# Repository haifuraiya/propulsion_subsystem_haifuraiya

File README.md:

# propulsion_subsystem_haifuraiya
# Introduction

This Open Research Institute Phase4SPace project repo will be used to develop the proposed Haifuraiya (Japanese:  ハイフライヤー English: High-Flyer) propulsion subsystem for a future HEO mission SmallSat. The repo was created on 8/28/2022.

# Summary

In July/August 2022 the ORI community discussed formalizing a concept for a High Energy Orbit (HEO) 'flyer' satellite, that would have its own propulsion system. The background for the Haifuraiya name and the overall initial concept derivation/top-level goals was discussed at length and is recorded[^1] and its predecessor concept by Jan King W3GEY is directly available[^2]. 

# Team

1. Samudra Haque N3RDX
2. Dan Schultz N8FGV
3. Thomas Denz, KC3ELI

# Special Notes

By special arrangement with its inventor/develpoer, ORI is making available in this repository a public copy of the entire flight hardware designs/firmware build knowledge-base including a comprehensive technical, scientific and industrial documentation set of [The George Washington University][100] [Micro-propulsion and Nanotechnology Laboratory][99]'s successful 2014-2015 BRICSAT-P (US Naval Academy/George Washington University) and 2014-2018 Canyval-X (Yonsei University/NASA GSFC/George Washington University) CubeSat quad-channel electric rocket system as provided in 2015 to NASA, on the condition that it is only used for study/research/experimentation/academic and scientific missions, and no commercial development is allowed. Parts of the technology have been patented (US Patent 10006445) and is available for licensing from The George Washington University. 

The knowledge-base is available [here][101]

If you choose to view/utilize the references (Approximately *3.14GB, 3525 files*), you are advised the knowledge-base contains copyrighted code, and information that was and still could be of a propietary nature thus may have more restrictive licenses than the license under which ORI has organized this repository. Your are restricted from disseminating this repository without the exact same restrictions you are being asked to follow. *While ORI has assurances the information will be able to be replicated (to build ground/engineering/flight hardware) with current production COTS parts -  there is no technical support provided, and all questions are to be redirected to the inventor/developer directly. Contact ORI for further details.* 

# References

[^1]: [Haifuraiya slide presentations (August 2022)][1]
[^2]: [HEO-F Mission Overview Space System Design Concept (November 3, 2014)]

[1:] https://github.com/phase4ground/documents/tree/master/Papers_Articles_Presentations/Slide_Presentations/haifuraiya/   
[2:] https://github.com/phase4ground/documents/blob/master/Papers_Articles_Presentations/Slide_Presentations/haifuraiya/HEO-F_Mission%20Overview.pptx  
[99:] https://mpnl.seas.gwu.edu/  
[100:] https://www.gwu.edu  
[101:] TBD

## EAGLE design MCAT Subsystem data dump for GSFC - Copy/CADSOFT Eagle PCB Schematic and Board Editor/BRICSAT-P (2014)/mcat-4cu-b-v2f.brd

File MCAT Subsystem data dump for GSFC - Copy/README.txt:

This folder is intended to assist NASA GSFC team in debugging/repairing/replacing MCAT Subsystem hardware for the CANYVAL-X mission.

Portions of the content are (c) The George Washington University, 2015. Patents-pending. Some of the information of this folder is covered under US Patent 20110258981 and US Patent Appl 14/462,127, and possibly others. 

Embedded Firmware included in this release is (c) The George Washington University, 2013-2015.

Release of this information to NASA has been cleared by GWU Office of Technology Transfer, to aid in troubleshooting the CANYVAL-X mission hardware.

For information about updated copyright/patent status please contact: 

Gus Williamson
Licensing Associate-Physical Sciences  | Office of Technology Transfer                      
The George Washington University  | 2033 K St, NW;  Suite 750; Washington, DC 20052
T: +1-202-994-8975  M: +1-443-824-9692  | Email: gwilliamson@gwu.edu

For technical information:

Michael Keidar
Professor of Mechanical and Aerospace Engineering
School of Engineering and Applied Science
Professor of Neurological Surgery, School of Medicine and Health Sciences
Director, GW Institute for Nanotechnology
The George Washington University
Science & Engineering Hall 3550
800 22nd Street, Northwest
Washington, DC 20052
tel: 202-994-6929; fax: 202-994-0238
email: keidar@gwu.edu
https://www.mpnl.seas.gwu.edu

Additional testing/analytical data can be obtained from:

Samudra Haque, Ph.D Candidate, Aerospace Engineering, samudra@gwu.edu, (202) 812-3325

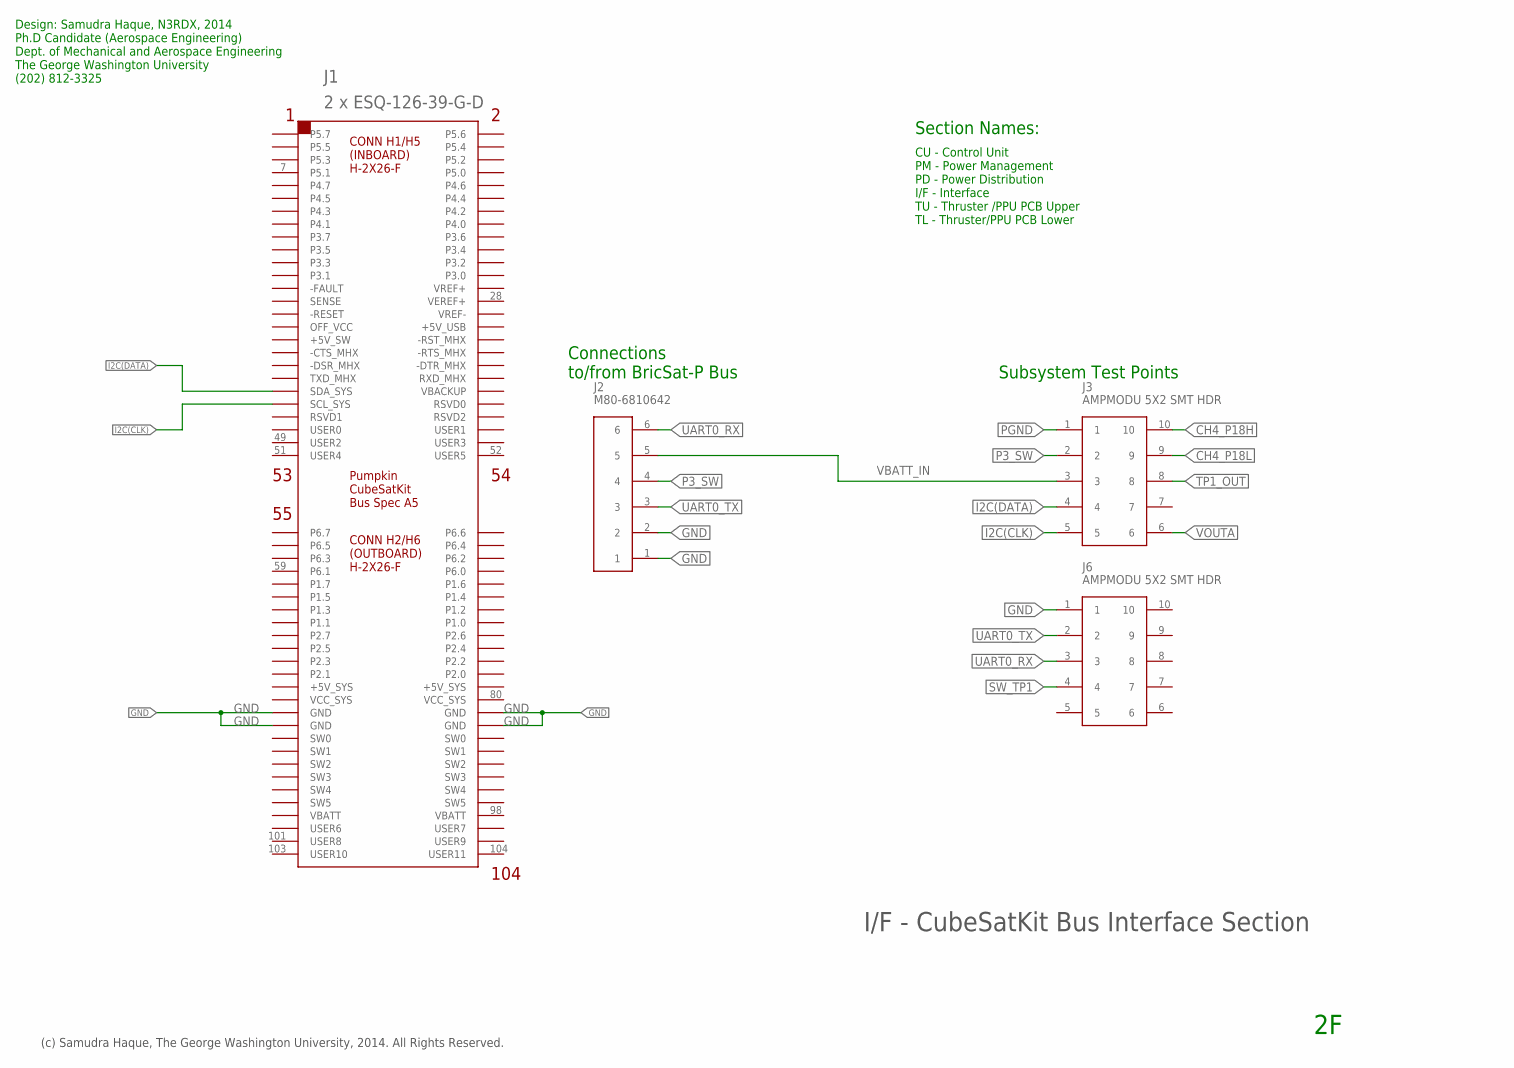
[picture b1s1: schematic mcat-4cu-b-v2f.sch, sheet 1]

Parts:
J1: 2 x ESQ-126-39-G-D; CSK-BUS-PKG
J2: M80-6810642; M80-68106
J3, J6: AMPMODU 5X2 SMT HDR; AMPMODU-SMT-PIN-HEADER-5X2

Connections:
CH4_P18H: J3.10; also elsewhere on the board
CH4_P18L: J3.9; also elsewhere on the board
GND: J1.81 (GND), J1.82 (GND), J1.83 (GND), J1.84 (GND), J2.1, J2.2, J6.1; also elsewhere on the board
I2C(CLK): J1.43 (SCL_SYS), J3.5; also elsewhere on the board
I2C(DATA): J1.41 (SDA_SYS), J3.4; also elsewhere on the board
P3_SW: J2.4, J3.2; also elsewhere on the board
PGND: J3.1; also elsewhere on the board
SW_TP1: J6.4; also elsewhere on the board
TP1_OUT: J3.8; also elsewhere on the board
UART0_RX: J2.6, J6.3; also elsewhere on the board
UART0_TX: J2.3, J6.2; also elsewhere on the board
VBATT_IN: J2.5, J3.3; also elsewhere on the board
VOUTA: J3.6; also elsewhere on the board

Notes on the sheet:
I/F - CubeSatKit Bus Interface Section
Subsystem Test Points
(c) Samudra Haque, The George Washington University, 2014. All Rights Reserved.
Connections to/from BricSat-P Bus
Design: Samudra Haque, N3RDX, 2014 Ph.D Candidate (Aerospace Engineering) Dept. of Mechanical and Aerospace Engineering The George Washington University (202) 812-3325
Section Names:
CU - Control Unit PM - Power Management PD - Power Distribution I/F - Interface TU - Thruster /PPU PCB Upper TL - Thruster/PPU PCB Lower

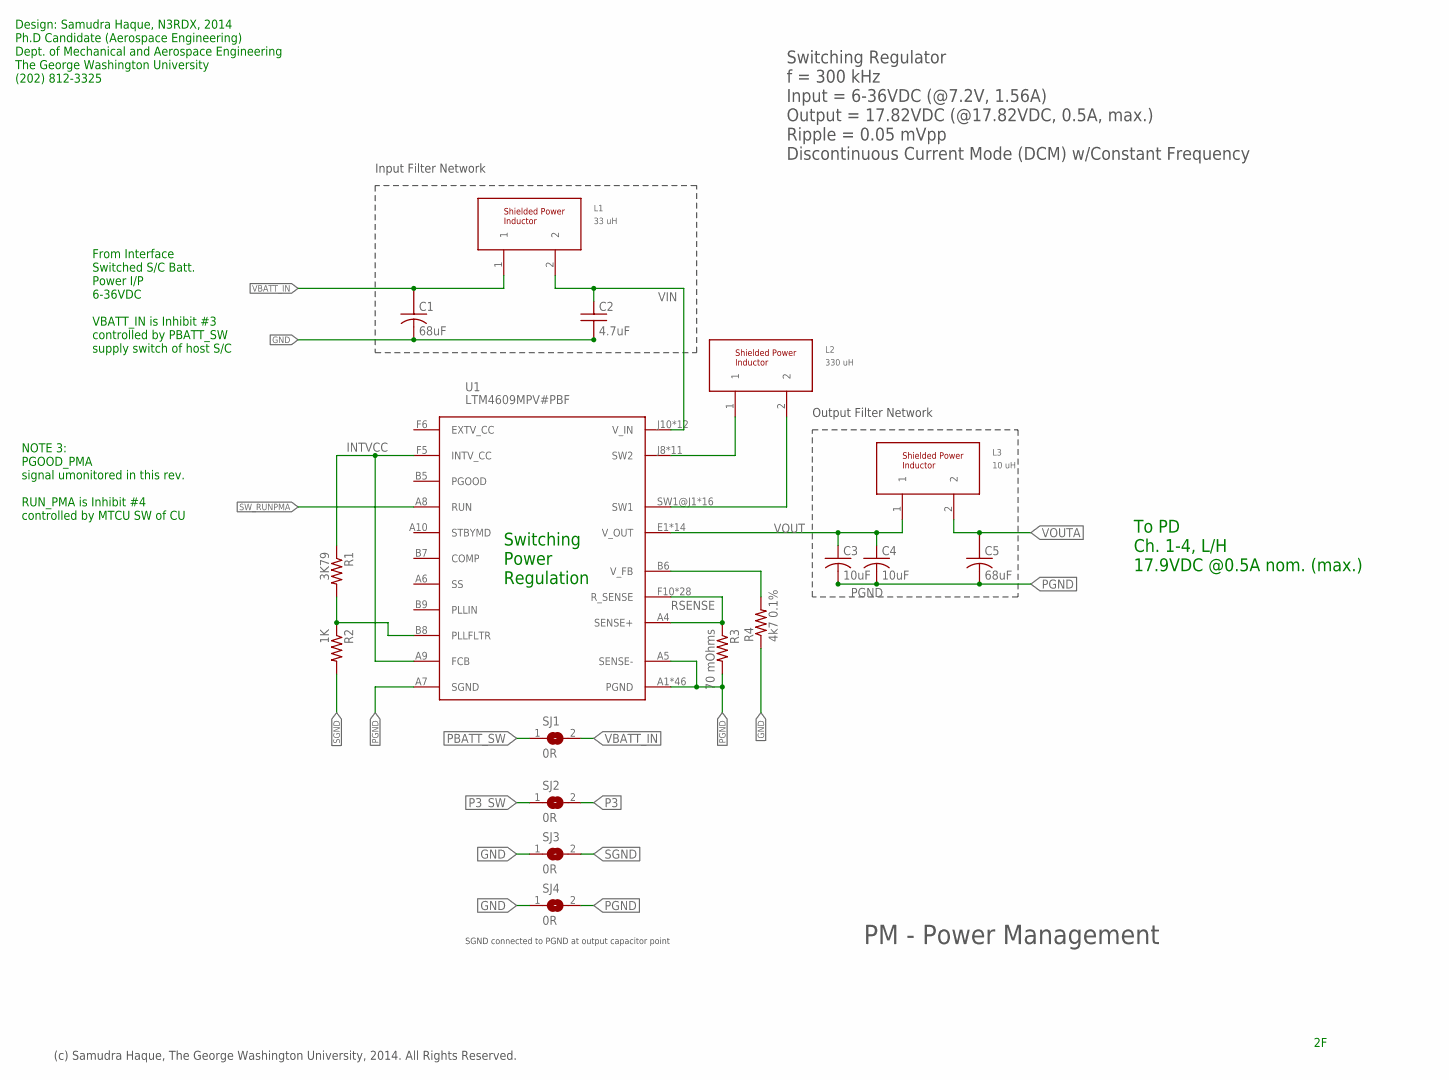
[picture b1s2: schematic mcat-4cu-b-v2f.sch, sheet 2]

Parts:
C1, C5: 68uF; OS-CON-SVPF-F12
C2: 4.7uF; MLCC-X7R-1210
C3, C4: 10uF; C1210K
L1: 33 uH; MSS1048
L2: 330 uH; MSS1048
L3: 10 uH; SERIES-POWER-INDUCTORS
R1: 3K79; R0805
R2: 1K; R0805
R3: 70 mOhms; R1206
R4: 4k7 0.1%; R0603
SJ1, SJ2, SJ3, SJ4: 0R; SJ
U1: LTM4609MPV#PBF; LGA-141-LTC-05-08-1840-B

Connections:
GND: C1.K1 (K), C2.2, R4.1, SJ3.1, SJ4.1; also elsewhere on the board
INTVCC: R1.1, U1.A9 (FCB), U1.F5 (INTV_CC)
P3: SJ2.2; also elsewhere on the board
P3_SW: SJ2.1; also elsewhere on the board
PBATT_SW: SJ1.1
PGND: C3.2, C4.2, C5.K1 (K), R3.2, SJ4.2, U1.A1 (PGND), U1.A2 (PGND), U1.A3 (PGND), U1.A5 (SENSE-), U1.A7 (SGND), U1.A11 (PGND), U1.A12 (PGND), U1.B1 (PGND), U1.B2 (PGND), U1.B3 (PGND), U1.B4 (PGND), U1.B10 (PGND), U1.B11 (PGND), U1.B12 (PGND), U1.C1 (PGND), U1.C2 (PGND), U1.C3 (PGND), U1.C4 (PGND), U1.C5 (PGND), U1.C6 (PGND), U1.C7 (PGND), U1.C8 (PGND), U1.C9 (PGND), U1.C10 (PGND), U1.C11 (PGND), U1.C12 (PGND), U1.D1 (PGND), U1.D2 (PGND), U1.D3 (PGND), U1.D4 (PGND), U1.D5 (PGND), U1.D6 (PGND), U1.D7 (PGND), U1.D8 (PGND), U1.D9 (PGND), U1.D10 (PGND), U1.D11 (PGND), U1.D12 (PGND), U1.E3 (PGND), U1.E4 (PGND), U1.E5 (PGND), U1.E6 (PGND), U1.E7 (PGND), U1.E8 (PGND), U1.E9 (PGND), U1.E10 (PGND), U1.E11 (PGND), U1.E12 (PGND); also elsewhere on the board
RSENSE: R3.1, U1.A4 (SENSE+), U1.F10 (R_SENSE), U1.F11 (R_SENSE), U1.F12 (R_SENSE), U1.G5 (R_SENSE), U1.G6 (R_SENSE), U1.G7 (R_SENSE), U1.G8 (R_SENSE), U1.G9 (R_SENSE), U1.G10 (R_SENSE), U1.G11 (R_SENSE), U1.G12 (R_SENSE), U1.H5 (R_SENSE), U1.H6 (R_SENSE), U1.H7 (R_SENSE), U1.H8 (R_SENSE), U1.H9 (R_SENSE), U1.H10 (R_SENSE), U1.H11 (R_SENSE), U1.H12 (R_SENSE), U1.J5 (R_SENSE), U1.J6 (R_SENSE), U1.J7 (R_SENSE), U1.K5 (R_SENSE), U1.K6 (R_SENSE), U1.L5 (R_SENSE), U1.L6 (R_SENSE), U1.M5 (R_SENSE), U1.M6 (R_SENSE)
SETFREQ: R1.2, R2.1, U1.B8 (PLLFLTR)
SGND: R2.2, SJ3.2; also elsewhere on the board
SW1: L2.2, U1.SW1@J1 (SW1), U1.SW1@J2 (SW1), U1.SW1@J3 (SW1), U1.SW1@J4 (SW1), U1.SW1@K1 (SW1), U1.SW1@K2 (SW1), U1.SW1@K3 (SW1), U1.SW1@K4 (SW1), U1.SW1@L1 (SW1), U1.SW1@L2 (SW1), U1.SW1@L3 (SW1), U1.SW1@L4 (SW1), U1.SW1@M1 (SW1), U1.SW1@M2 (SW1), U1.SW1@M3 (SW1), U1.SW1@M4 (SW1)
SW2: L2.1, U1.J8 (SW2), U1.J9 (SW2), U1.K7 (SW2), U1.K8 (SW2), U1.K9 (SW2), U1.L7 (SW2), U1.L8 (SW2), U1.L9 (SW2), U1.M7 (SW2), U1.M8 (SW2), U1.M9 (SW2)
SW_RUNPMA: U1.A8 (RUN); also elsewhere on the board
VBATT_IN: C1.A1 (A), L1.1, SJ1.2; also elsewhere on the board
VFB: R4.2, U1.B6 (V_FB)
VIN: C2.1, L1.2, U1.J10 (V_IN), U1.J11 (V_IN), U1.J12 (V_IN), U1.K10 (V_IN), U1.K11 (V_IN), U1.K12 (V_IN), U1.L10 (V_IN), U1.L11 (V_IN), U1.L12 (V_IN), U1.M10 (V_IN), U1.M11 (V_IN), U1.M12 (V_IN)
VOUT: C3.1, C4.1, L3.1, U1.E1 (V_OUT), U1.E2 (V_OUT), U1.F1 (V_OUT), U1.F2 (V_OUT), U1.F3 (V_OUT), U1.F4 (V_OUT), U1.G1 (V_OUT), U1.G2 (V_OUT), U1.G3 (V_OUT), U1.G4 (V_OUT), U1.H2 (V_OUT), U1.H3 (V_OUT), U1.H4 (V_OUT), U1.VOUT (V_OUT)
VOUTA: C5.A1 (A), L3.2; also elsewhere on the board

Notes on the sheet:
PM - Power Management
Input Filter Network
SGND connected to PGND at output capacitor point
Output Filter Network
Switching Regulator f = 300 kHz Input = 6-36VDC (@7.2V, 1.56A) Output = 17.82VDC (@17.82VDC, 0.5A, max.) Ripple = 0.05 mVpp Discontinuous Current Mode (DCM) w/Constant Frequency
(c) Samudra Haque, The George Washington University, 2014. All Rights Reserved.
NOTE 3: PGOOD_PMA signal umonitored in this rev. RUN_PMA is Inhibit #4 controlled by MTCU SW of CU
Switching Power Regulation
To PD Ch. 1-4, L/H 17.9VDC @0.5A nom. (max.)
From Interface Switched S/C Batt. Power I/P 6-36VDC VBATT_IN is Inhibit #3 controlled by PBATT_SW supply switch of host S/C
Design: Samudra Haque, N3RDX, 2014 Ph.D Candidate (Aerospace Engineering) Dept. of Mechanical and Aerospace Engineering The George Washington University (202) 812-3325

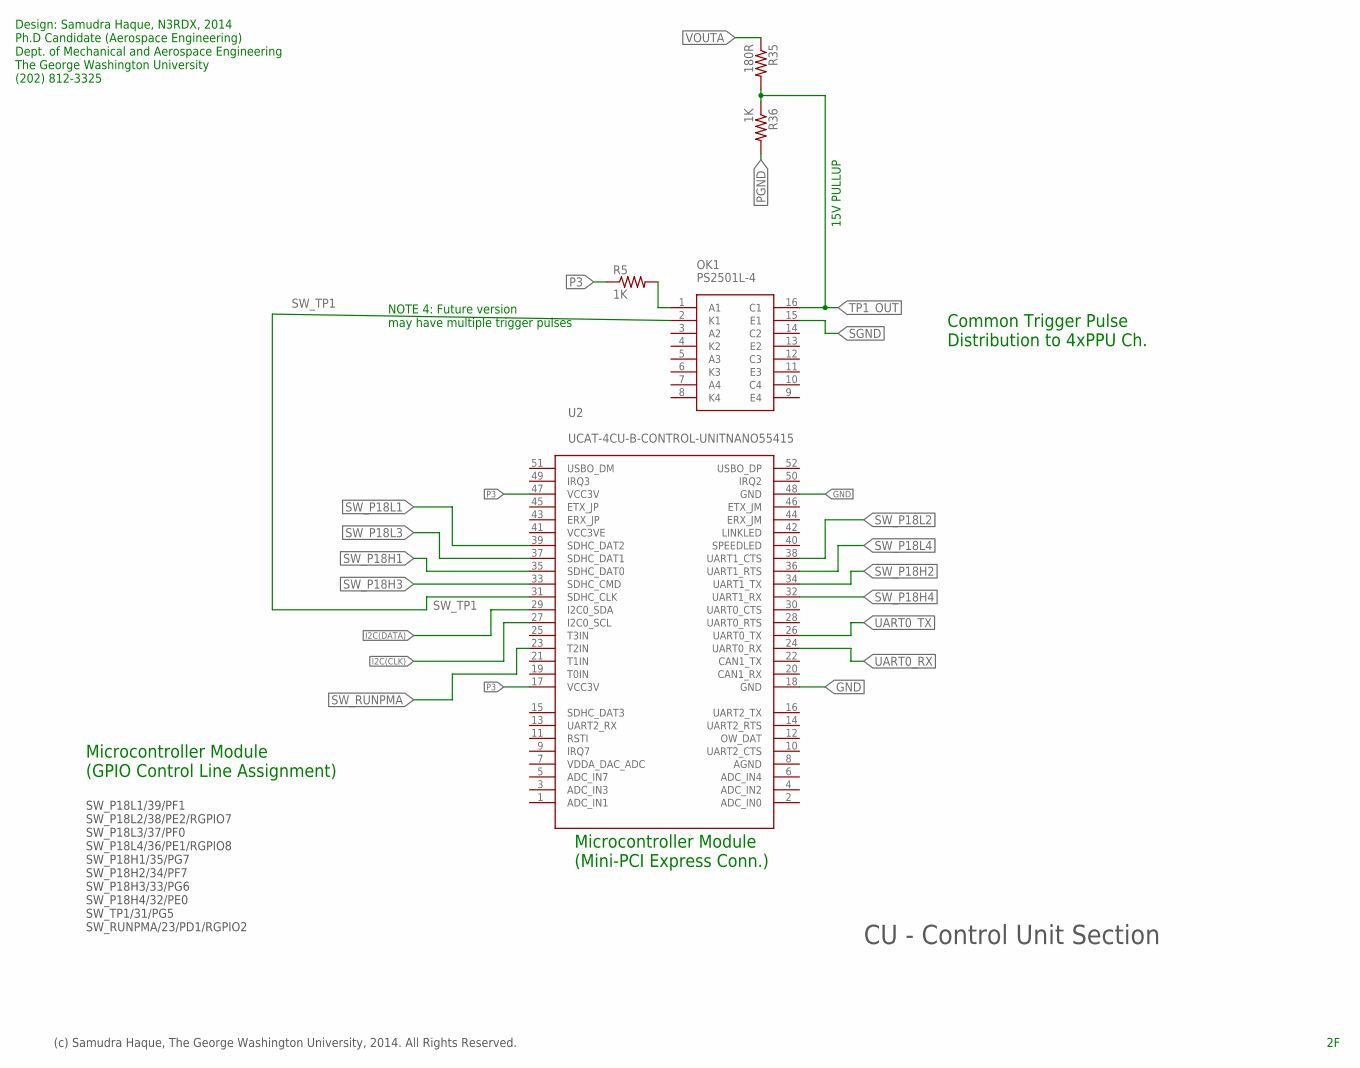
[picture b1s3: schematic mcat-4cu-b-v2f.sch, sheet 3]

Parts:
OK1: PS2501L-4
R5, R36: 1K; R0805
R35: 180R; R0805
U2: UCAT-4CU-B-CONTROL-UNITNANO55415; MOLEX-MINI-PCI-EXPRESS-8MM-52CKT

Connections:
GND: U2.18 (GND), U2.48 (GND); also elsewhere on the board
I2C(CLK): U2.27 (I2C0_SCL); also elsewhere on the board
I2C(DATA): U2.29 (I2C0_SDA); also elsewhere on the board
unnamed: OK1.1 (A1), R5.2
P3: R5.1, U2.17 (VCC3V), U2.47 (VCC3V); also elsewhere on the board
PGND: R36.2; also elsewhere on the board
SGND: OK1.15 (E1); also elsewhere on the board
SW_P18H1: U2.35 (SDHC_DAT0); also elsewhere on the board
SW_P18H2: U2.34 (UART1_TX); also elsewhere on the board
SW_P18H3: U2.33 (SDHC_CMD); also elsewhere on the board
SW_P18H4: U2.32 (UART1_RX); also elsewhere on the board
SW_P18L1: U2.39 (SDHC_DAT2); also elsewhere on the board
SW_P18L2: U2.38 (UART1_CTS); also elsewhere on the board
SW_P18L3: U2.37 (SDHC_DAT1); also elsewhere on the board
SW_P18L4: U2.36 (UART1_RTS); also elsewhere on the board
SW_RUNPMA: U2.23 (T2IN); also elsewhere on the board
SW_TP1: OK1.2 (K1), U2.31 (SDHC_CLK); also elsewhere on the board
TP1_OUT: OK1.16 (C1), R35.2, R36.1; also elsewhere on the board
UART0_RX: U2.24 (UART0_RX); also elsewhere on the board
UART0_TX: U2.26 (UART0_TX); also elsewhere on the board
VOUTA: R35.1; also elsewhere on the board

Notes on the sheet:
CU - Control Unit Section
SW_P18L1/39/PF1 SW_P18L2/38/PE2/RGPIO7 SW_P18L3/37/PF0 SW_P18L4/36/PE1/RGPIO8 SW_P18H1/35/PG7 SW_P18H2/34/PF7 SW_P18H3/33/PG6 SW_P18H4/32/PE0 SW_TP1/31/PG5 SW_RUNPMA/23/PD1/RGPIO2
(c) Samudra Haque, The George Washington University, 2014. All Rights Reserved.
Microcontroller Module (Mini-PCI Express Conn.)
Common Trigger Pulse Distribution to 4xPPU Ch.
NOTE 4: Future version may have multiple trigger pulses
Microcontroller Module (GPIO Control Line Assignment)
Design: Samudra Haque, N3RDX, 2014 Ph.D Candidate (Aerospace Engineering) Dept. of Mechanical and Aerospace Engineering The George Washington University (202) 812-3325
15V PULLUP

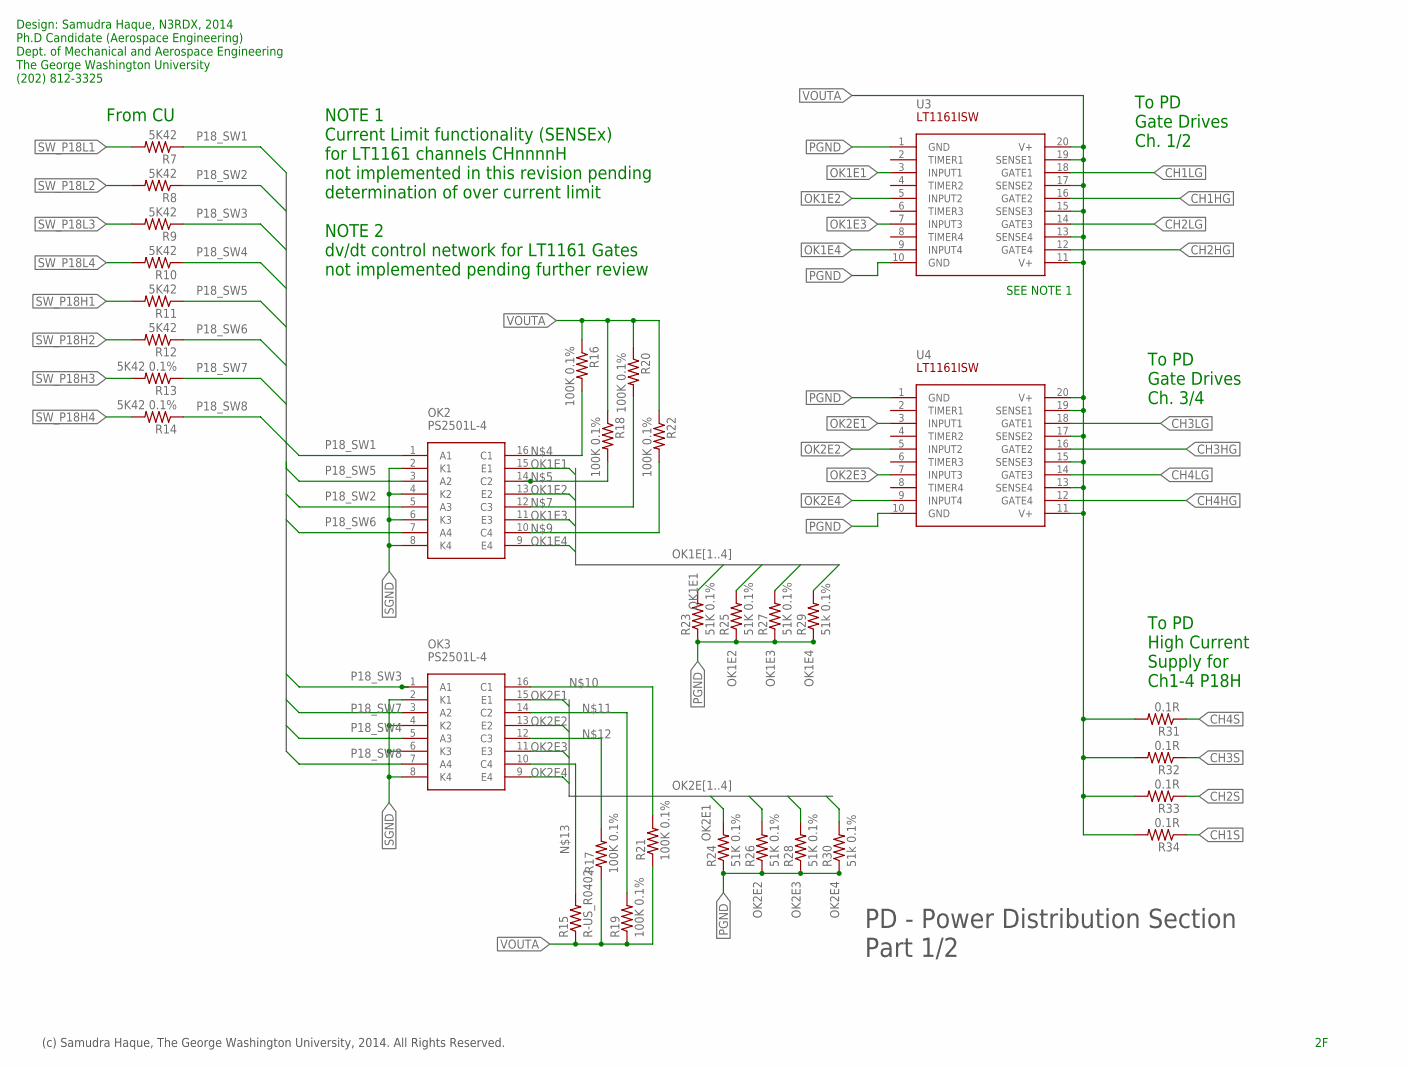
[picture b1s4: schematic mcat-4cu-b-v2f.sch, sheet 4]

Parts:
OK2, OK3: PS2501L-4
R7, R8, R9, R10, R11, R12: 5K42; R1206
R13, R14: 5K42 0.1%; R1206
R15: R-US_R0402; R0402
R16, R17, R18, R19, R20, R21, R22: 100K 0.1%; R0402
R23, R24, R25, R26, R27, R28: 51K 0.1%; R0603
R29, R30: 51k 0.1%; R0603
R31, R32, R33, R34: 0.1R; R0402
U3, U4: LT1161ISW; 20-LEAD-PLASTIC-SO

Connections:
CH1HG: U3.16 (GATE2); also elsewhere on the board
CH1LG: U3.18 (GATE1); also elsewhere on the board
CH1S: R34.1; also elsewhere on the board
CH2HG: U3.12 (GATE4); also elsewhere on the board
CH2LG: U3.14 (GATE3); also elsewhere on the board
CH2S: R33.1; also elsewhere on the board
CH3HG: U4.16 (GATE2); also elsewhere on the board
CH3LG: U4.18 (GATE1); also elsewhere on the board
CH3S: R32.1; also elsewhere on the board
CH4HG: U4.12 (GATE4); also elsewhere on the board
CH4LG: U4.14 (GATE3); also elsewhere on the board
CH4S: R31.1; also elsewhere on the board
unnamed: OK2.16 (C1), R16.2
unnamed: OK2.14 (C2), R18.2
unnamed: OK2.12 (C3), R20.2
unnamed: OK2.10 (C4), R22.2
unnamed: OK3.16 (C1), R21.2
unnamed: OK3.14 (C2), R19.2
unnamed: OK3.12 (C3), R17.2
unnamed: OK3.10 (C4), R15.2
OK1E1: OK2.15 (E1), R23.2, U3.3 (INPUT1)
OK1E2: OK2.13 (E2), R25.2, U3.5 (INPUT2)
OK1E3: OK2.11 (E3), R27.2, U3.7 (INPUT3)
OK1E4: OK2.9 (E4), R29.2, U3.9 (INPUT4)
OK2E1: OK3.15 (E1), R24.2, U4.3 (INPUT1)
OK2E2: OK3.13 (E2), R26.2, U4.5 (INPUT2)
OK2E3: OK3.11 (E3), R28.2, U4.7 (INPUT3)
OK2E4: OK3.9 (E4), R30.2, U4.9 (INPUT4)
P18_SW1: OK2.1 (A1), R7.1
P18_SW2: OK2.5 (A3), R8.1
P18_SW3: OK3.1 (A1), R9.1
P18_SW4: OK3.5 (A3), R10.1
P18_SW5: OK2.3 (A2), R11.1
P18_SW6: OK2.7 (A4), R12.1
P18_SW7: OK3.3 (A2), R13.1
P18_SW8: OK3.7 (A4), R14.1
PGND: R23.1, R24.1, R25.1, R26.1, R27.1, R28.1, R29.1, R30.1, U3.1 (GND), U3.10 (GND), U4.1 (GND), U4.10 (GND); also elsewhere on the board
SGND: OK2.2 (K1), OK2.4 (K2), OK2.6 (K3), OK2.8 (K4), OK3.2 (K1), OK3.4 (K2), OK3.6 (K3), OK3.8 (K4); also elsewhere on the board
SW_P18H1: R11.2; also elsewhere on the board
SW_P18H2: R12.2; also elsewhere on the board
SW_P18H3: R13.2; also elsewhere on the board
SW_P18H4: R14.2; also elsewhere on the board
SW_P18L1: R7.2; also elsewhere on the board
SW_P18L2: R8.2; also elsewhere on the board
SW_P18L3: R9.2; also elsewhere on the board
SW_P18L4: R10.2; also elsewhere on the board
VOUTA: R15.1, R16.1, R17.1, R18.1, R19.1, R20.1, R21.1, R22.1, R31.2, R32.2, R33.2, R34.2, U3.11 (V+), U3.13 (SENSE4), U3.15 (SENSE3), U3.17 (SENSE2), U3.19 (SENSE1), U3.20 (V+), U4.11 (V+), U4.13 (SENSE4), U4.15 (SENSE3), U4.17 (SENSE2), U4.19 (SENSE1), U4.20 (V+); also elsewhere on the board

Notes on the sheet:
PD - Power Distribution Section Part 1/2
NOTE 1 Current Limit functionality (SENSEx) for LT1161 channels CHnnnnH not implemented in this revision pending determination of over current limit NOTE 2 dv/dt control network for LT1161 Gates not implemented pending further review
SEE NOTE 1
(c) Samudra Haque, The George Washington University, 2014. All Rights Reserved.
From CU
To PD Gate Drives Ch. 1/2
To PD High Current Supply for Ch1-4 P18H
To PD Gate Drives Ch. 3/4
Design: Samudra Haque, N3RDX, 2014 Ph.D Candidate (Aerospace Engineering) Dept. of Mechanical and Aerospace Engineering The George Washington University (202) 812-3325

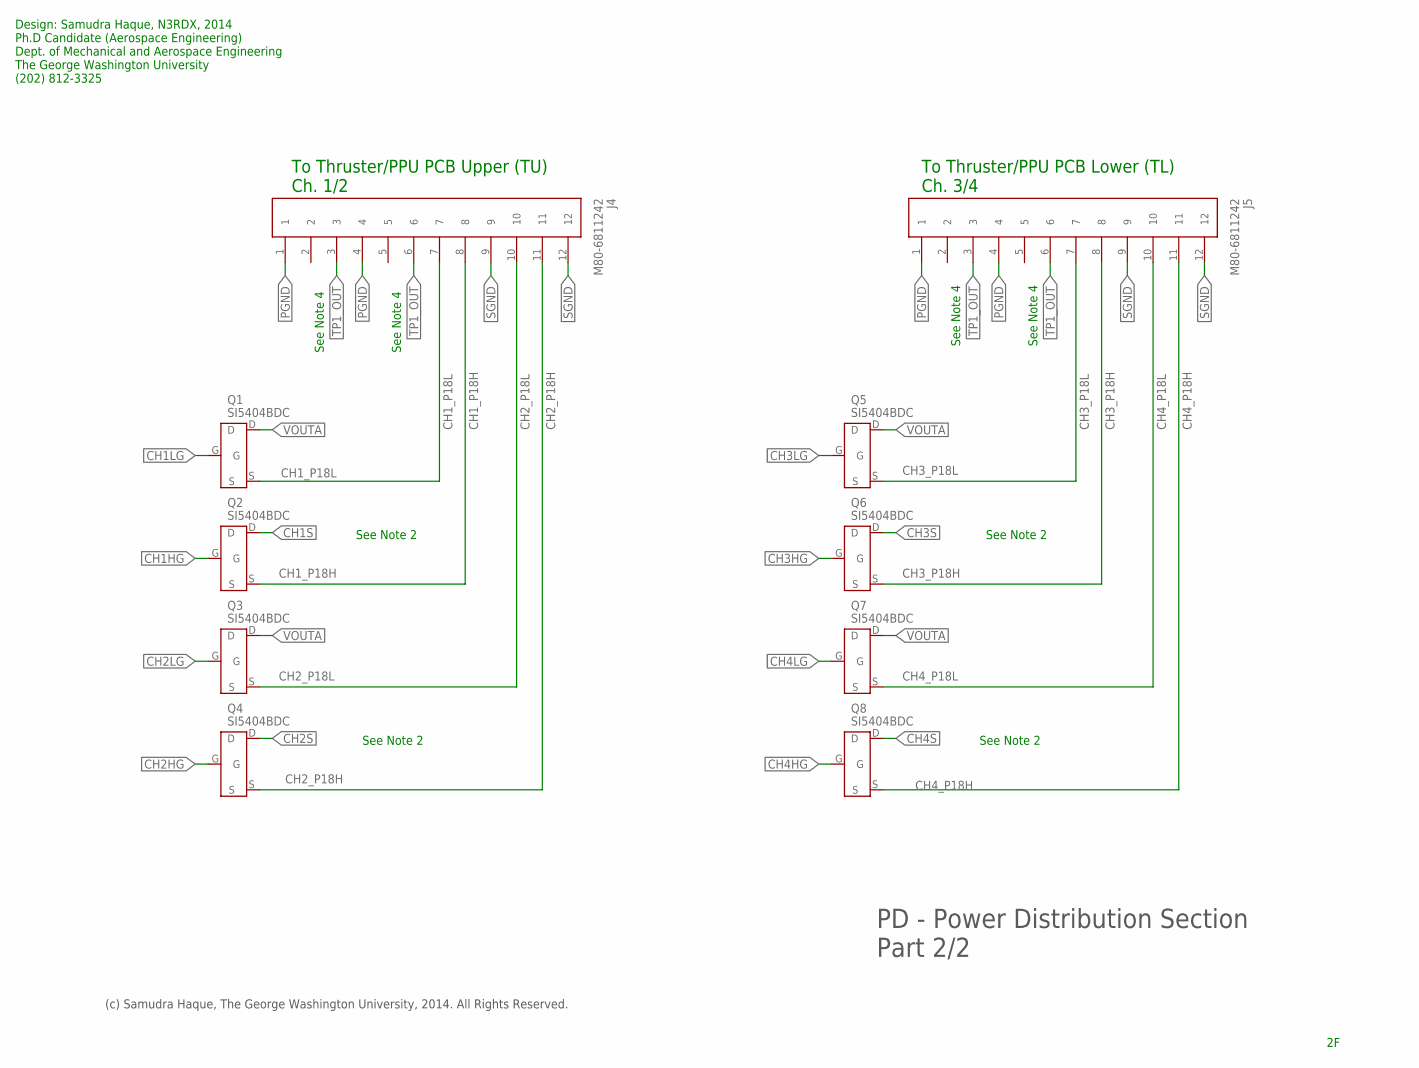
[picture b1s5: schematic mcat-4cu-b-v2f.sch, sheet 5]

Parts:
J4, J5: M80-6811242; M80-68112
Q1, Q2, Q3, Q4, Q5, Q6, Q7, Q8: SI5404BDC; 1206-8-CHIPFET

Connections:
CH1HG: Q2.G; also elsewhere on the board
CH1LG: Q1.G; also elsewhere on the board
CH1S: Q2.D; also elsewhere on the board
CH1_P18H: J4.8, Q2.S
CH1_P18L: J4.7, Q1.S
CH2HG: Q4.G; also elsewhere on the board
CH2LG: Q3.G; also elsewhere on the board
CH2S: Q4.D; also elsewhere on the board
CH2_P18H: J4.11, Q4.S
CH2_P18L: J4.10, Q3.S
CH3HG: Q6.G; also elsewhere on the board
CH3LG: Q5.G; also elsewhere on the board
CH3S: Q6.D; also elsewhere on the board
CH3_P18H: J5.8, Q6.S
CH3_P18L: J5.7, Q5.S
CH4HG: Q8.G; also elsewhere on the board
CH4LG: Q7.G; also elsewhere on the board
CH4S: Q8.D; also elsewhere on the board
CH4_P18H: J5.11, Q8.S; also elsewhere on the board
CH4_P18L: J5.10, Q7.S; also elsewhere on the board
PGND: J4.1, J4.4, J5.1, J5.4; also elsewhere on the board
SGND: J4.9, J4.12, J5.9, J5.12; also elsewhere on the board
TP1_OUT: J4.3, J4.6, J5.3, J5.6; also elsewhere on the board
VOUTA: Q1.D, Q3.D, Q5.D, Q7.D; also elsewhere on the board

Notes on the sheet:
PD - Power Distribution Section Part 2/2
(c) Samudra Haque, The George Washington University, 2014. All Rights Reserved.
See Note 2
To Thruster/PPU PCB Upper (TU) Ch. 1/2
To Thruster/PPU PCB Lower (TL) Ch. 3/4
See Note 4
Design: Samudra Haque, N3RDX, 2014 Ph.D Candidate (Aerospace Engineering) Dept. of Mechanical and Aerospace Engineering The George Washington University (202) 812-3325

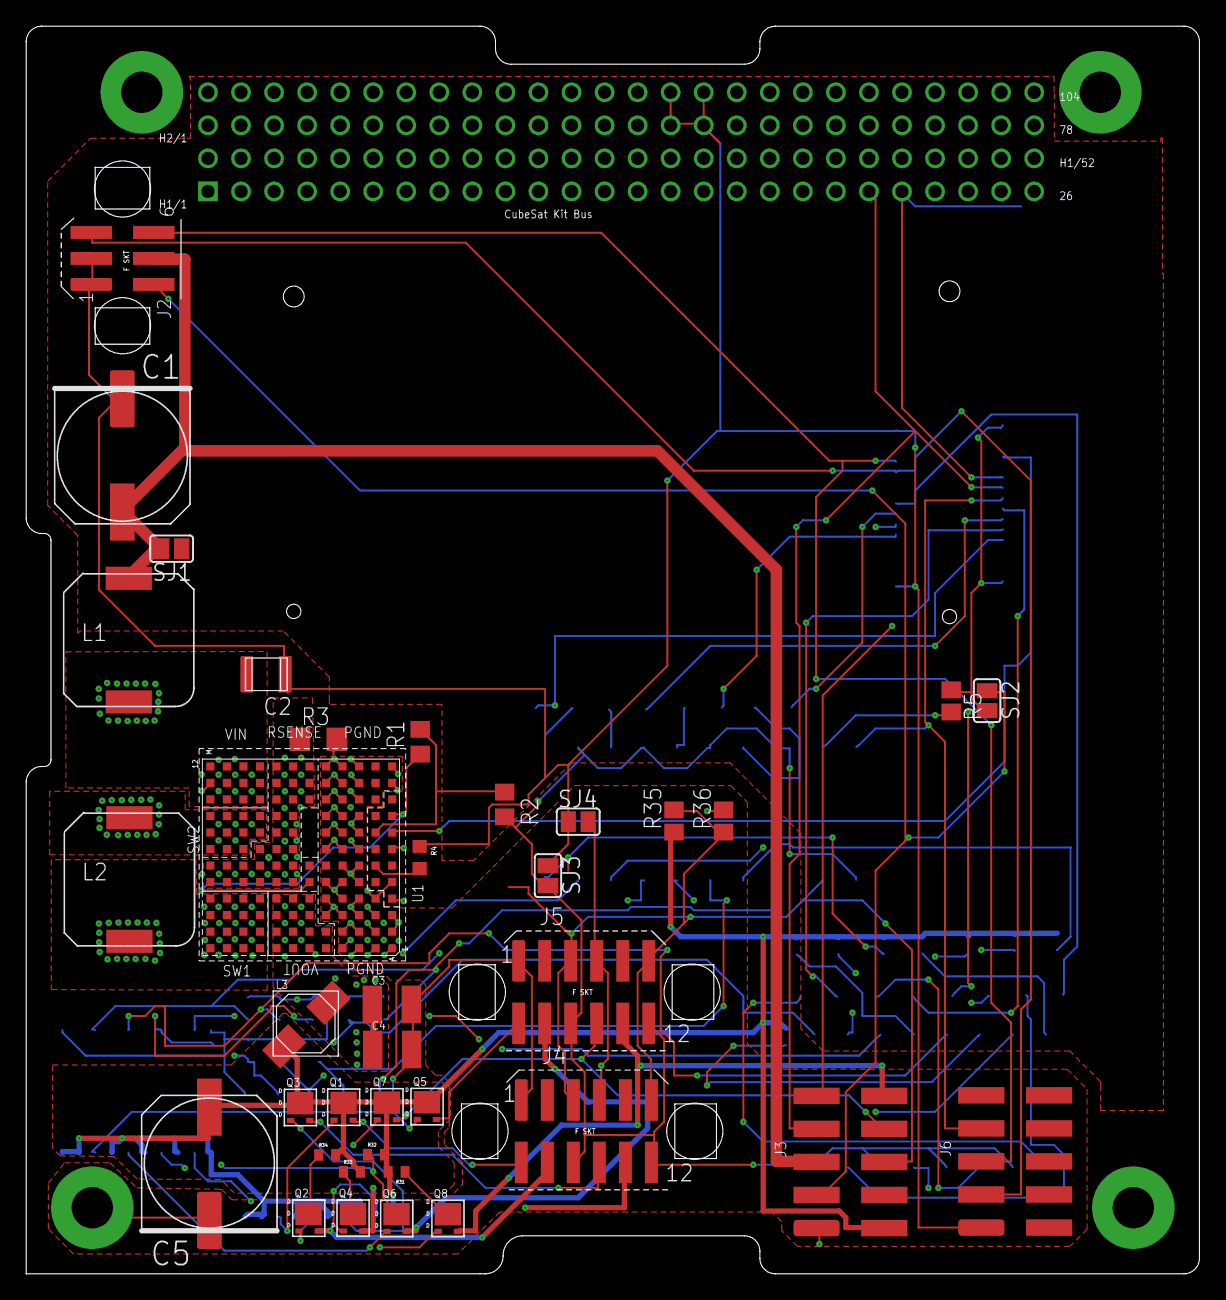
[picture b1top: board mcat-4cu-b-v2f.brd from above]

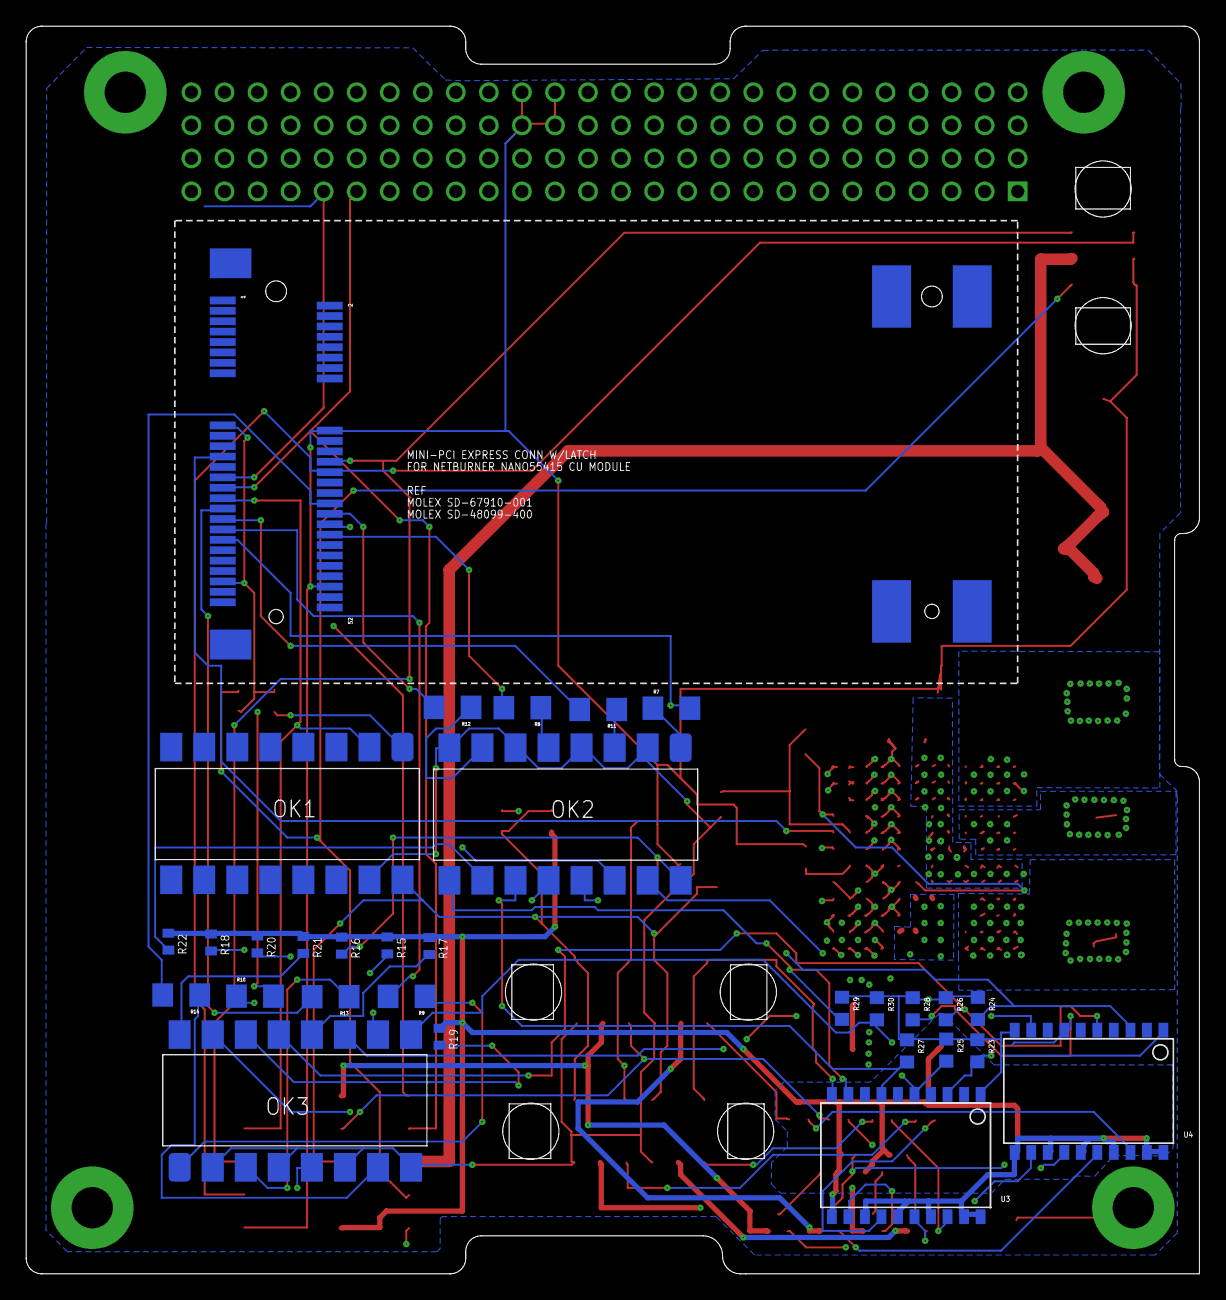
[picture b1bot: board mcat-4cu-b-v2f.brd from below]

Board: 4 copper layers, 90.2 x 95.9 mm, 68 parts (30 on the bottom side), 75 nets.

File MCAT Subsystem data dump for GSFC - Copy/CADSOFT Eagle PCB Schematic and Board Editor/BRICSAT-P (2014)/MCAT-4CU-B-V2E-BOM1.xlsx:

Part | Value | Device | Package | Description | MF | MPN | OC_FARNELL
C1 | 68uF | OSCON-50SVPF68M | OS-CON-SVPF-F12
C2 | 4.7uF | AVX-LD105C475KAB2A | MLCC-X7R-1210
C3 | 10uF | C-USC1210K | C1210K | CAPACITOR, American symbol
C4 | 10uF | C-USC1210K | C1210K | CAPACITOR, American symbol
C5 | 68uF | OSCON-50SVPF68M | OS-CON-SVPF-F12
H1 | MOUNT-PAD-ROUNDCSK_MTG_HOLE_A5 | MOUNT-PAD-ROUNDCSK_MTG_HOLE_A5 | CSK_MOUNTING_HOLE | MOUNTING PAD, round
H2 | MOUNT-PAD-ROUNDCSK_MTG_HOLE_A5 | MOUNT-PAD-ROUNDCSK_MTG_HOLE_A5 | CSK_MOUNTING_HOLE | MOUNTING PAD, round
H3 | MOUNT-PAD-ROUNDCSK_MTG_HOLE_A5 | MOUNT-PAD-ROUNDCSK_MTG_HOLE_A5 | CSK_MOUNTING_HOLE | MOUNTING PAD, round
HBL | MOUNT-PAD-ROUNDCSK_MTG_HOLE_A5 | MOUNT-PAD-ROUNDCSK_MTG_HOLE_A5 | CSK_MOUNTING_HOLE | MOUNTING PAD, round
J1 | 2 x ESQ-126-39-G-D | CSK-BUS-CONN2X2X26 | CSK-BUS-PKG | Cubesat Kit Bus Connector
J2 | M80-6810642 | M80-6810642 | M80-68106
J3 | AMPMODU 5X2 SMT HDR | AMPMODU-5-146131-X(5X2) | AMPMODU-SMT-PIN-HEADER-5X2
J4 | M80-6811242 | M80-6811242 | M80-68112
J5 | M80-6811242 | M80-6811242 | M80-68112
L1 | 33 uH | MSS1038-333ML_ | MSS1048
L2 | 330 uH | MSS1048-334KL_ | MSS1048
L3 | 10 uH | ELL-5PS100M | SERIES-POWER-INDUCTORS |  | PANASONIC | ELL5PS100M | 1717452
OK1 | PS2501L-4 | PS2501L-4 | PS2501L-4
OK2 | PS2501L-4 | PS2501L-4 | PS2501L-4
OK3 | PS2501L-4 | PS2501L-4 | PS2501L-4
Q1 | SI5404BDC | SI5404BDC | 1206-8-CHIPFET
Q2 | SI5404BDC | SI5404BDC | 1206-8-CHIPFET
Q3 | SI5404BDC | SI5404BDC | 1206-8-CHIPFET
Q4 | SI5404BDC | SI5404BDC | 1206-8-CHIPFET
Q5 | SI5404BDC | SI5404BDC | 1206-8-CHIPFET
Q6 | SI5404BDC | SI5404BDC | 1206-8-CHIPFET
Q7 | SI5404BDC | SI5404BDC | 1206-8-CHIPFET
Q8 | SI5404BDC | SI5404BDC | 1206-8-CHIPFET
R1 | 3K79 | R-US_R0805 | R0805 | RESISTOR, American symbol
R2 | 1K | R-US_R0805 | R0805 | RESISTOR, American symbol
R3 | 70 mOhms | R-US_R1206 | R1206 | RESISTOR, American symbol
R4 | 4k7 0.1% | R-US_R0603 | R0603 | RESISTOR, American symbol
R5 | 1K | R-US_R0805 | R0805 | RESISTOR, American symbol
R6 | 604R | R-US_R0805 | R0805 | RESISTOR, American symbol
R7 | 5K42 | R-US_R1206 | R1206 | RESISTOR, American symbol
R8 | 5K42 | R-US_R1206 | R1206 | RESISTOR, American symbol
R9 | 5K42 | R-US_R1206 | R1206 | RESISTOR, American symbol
R10 | 5K42 | R-US_R1206 | R1206 | RESISTOR, American symbol
R11 | 5K42 | R-US_R1206 | R1206 | RESISTOR, American symbol
R12 | 5K42 | R-US_R1206 | R1206 | RESISTOR, American symbol
R13 | 5K42 0.1% | R-US_R1206 | R1206 | RESISTOR, American symbol
R14 | 5K42 0.1% | R-US_R1206 | R1206 | RESISTOR, American symbol
R15 | R-US_R0402 | R-US_R0402 | R0402 | RESISTOR, American symbol
R16 | 100K 0.1% | R-US_R0402 | R0402 | RESISTOR, American symbol
R17 | 100K 0.1% | R-US_R0402 | R0402 | RESISTOR, American symbol
R18 | 100K 0.1% | R-US_R0402 | R0402 | RESISTOR, American symbol
R19 | 100K 0.1% | R-US_R0402 | R0402 | RESISTOR, American symbol
R20 | 100K 0.1% | R-US_R0402 | R0402 | RESISTOR, American symbol
R21 | 100K 0.1% | R-US_R0402 | R0402 | RESISTOR, American symbol
R22 | 100K 0.1% | R-US_R0402 | R0402 | RESISTOR, American symbol
R23 | 51K 0.1% | R-US_R0603 | R0603 | RESISTOR, American symbol
R24 | 51K 0.1% | R-US_R0603 | R0603 | RESISTOR, American symbol
R25 | 51K 0.1% | R-US_R0603 | R0603 | RESISTOR, American symbol
R26 | 51K 0.1% | R-US_R0603 | R0603 | RESISTOR, American symbol
R27 | 51K 0.1% | R-US_R0603 | R0603 | RESISTOR, American symbol
R28 | 51K 0.1% | R-US_R0603 | R0603 | RESISTOR, American symbol
R29 | 51k 0.1% | R-US_R0603 | R0603 | RESISTOR, American symbol
R30 | 51k 0.1% | R-US_R0603 | R0603 | RESISTOR, American symbol
R31 | 0.1R 1% PTC | R-US_R0402 | R0402 | RESISTOR, American symbol
R32 | 0.1R 1% PTC | R-US_R0402 | R0402 | RESISTOR, American symbol
R33 | 0.1R 1% PTC | R-US_R0402 | R0402 | RESISTOR, American symbol
R34 | 0.1R 1% PTC | R-US_R0402 | R0402 | RESISTOR, American symbol
SJ1 | 0R | SJ | SJ | SMD solder JUMPER
SJ2 | 0R | SJ | SJ | SMD solder JUMPER
SJ3 | 0R | SJ | SJ | SMD solder JUMPER
SJ4 | 0R | SJ | SJ | SMD solder JUMPER
U1 | LTM4609MPV#PBF | LTM4609MPV#PBFROHS/HITEMP | LGA-141-LTC-05-08-1840-B | Per LTC Datasheet 4609fe LTM4609 (c) Samudra Haque, N3RDX, 2/23/2014
U2 | UCAT-4CU-B-CONTROL-UNITNANO55415 | UCAT-4CU-B-CONTROL-UNITNANO55415 | MOLEX-MINI-PCI-EXPRESS-8MM-52CKT
U3 | LT1161ISW | LT1161ISW | 20-LEAD-PLASTIC-SO
U4 | LT1161ISW | LT1161ISW | 20-LEAD-PLASTIC-SO

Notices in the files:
MCAT Subsystem data dump for GSFC - Copy/Embedded Firmware/main5.cpp:
Copyright 2014-2015 The George Washington University. ALL RIGHTS RESERVED. Patents Pending
Copyright 1998-2013 NetBurner, Inc.  ALL RIGHTS RESERVED
parts and their libraries:
COPYRIGHT: (c) 2015, GWU
COPYRIGHT: (c) 2015, THE GEORGE WASHINGTON UNIVERSITY
COPYRIGHT: (c) 2015, The George Washington University. All Rights Reserved.
